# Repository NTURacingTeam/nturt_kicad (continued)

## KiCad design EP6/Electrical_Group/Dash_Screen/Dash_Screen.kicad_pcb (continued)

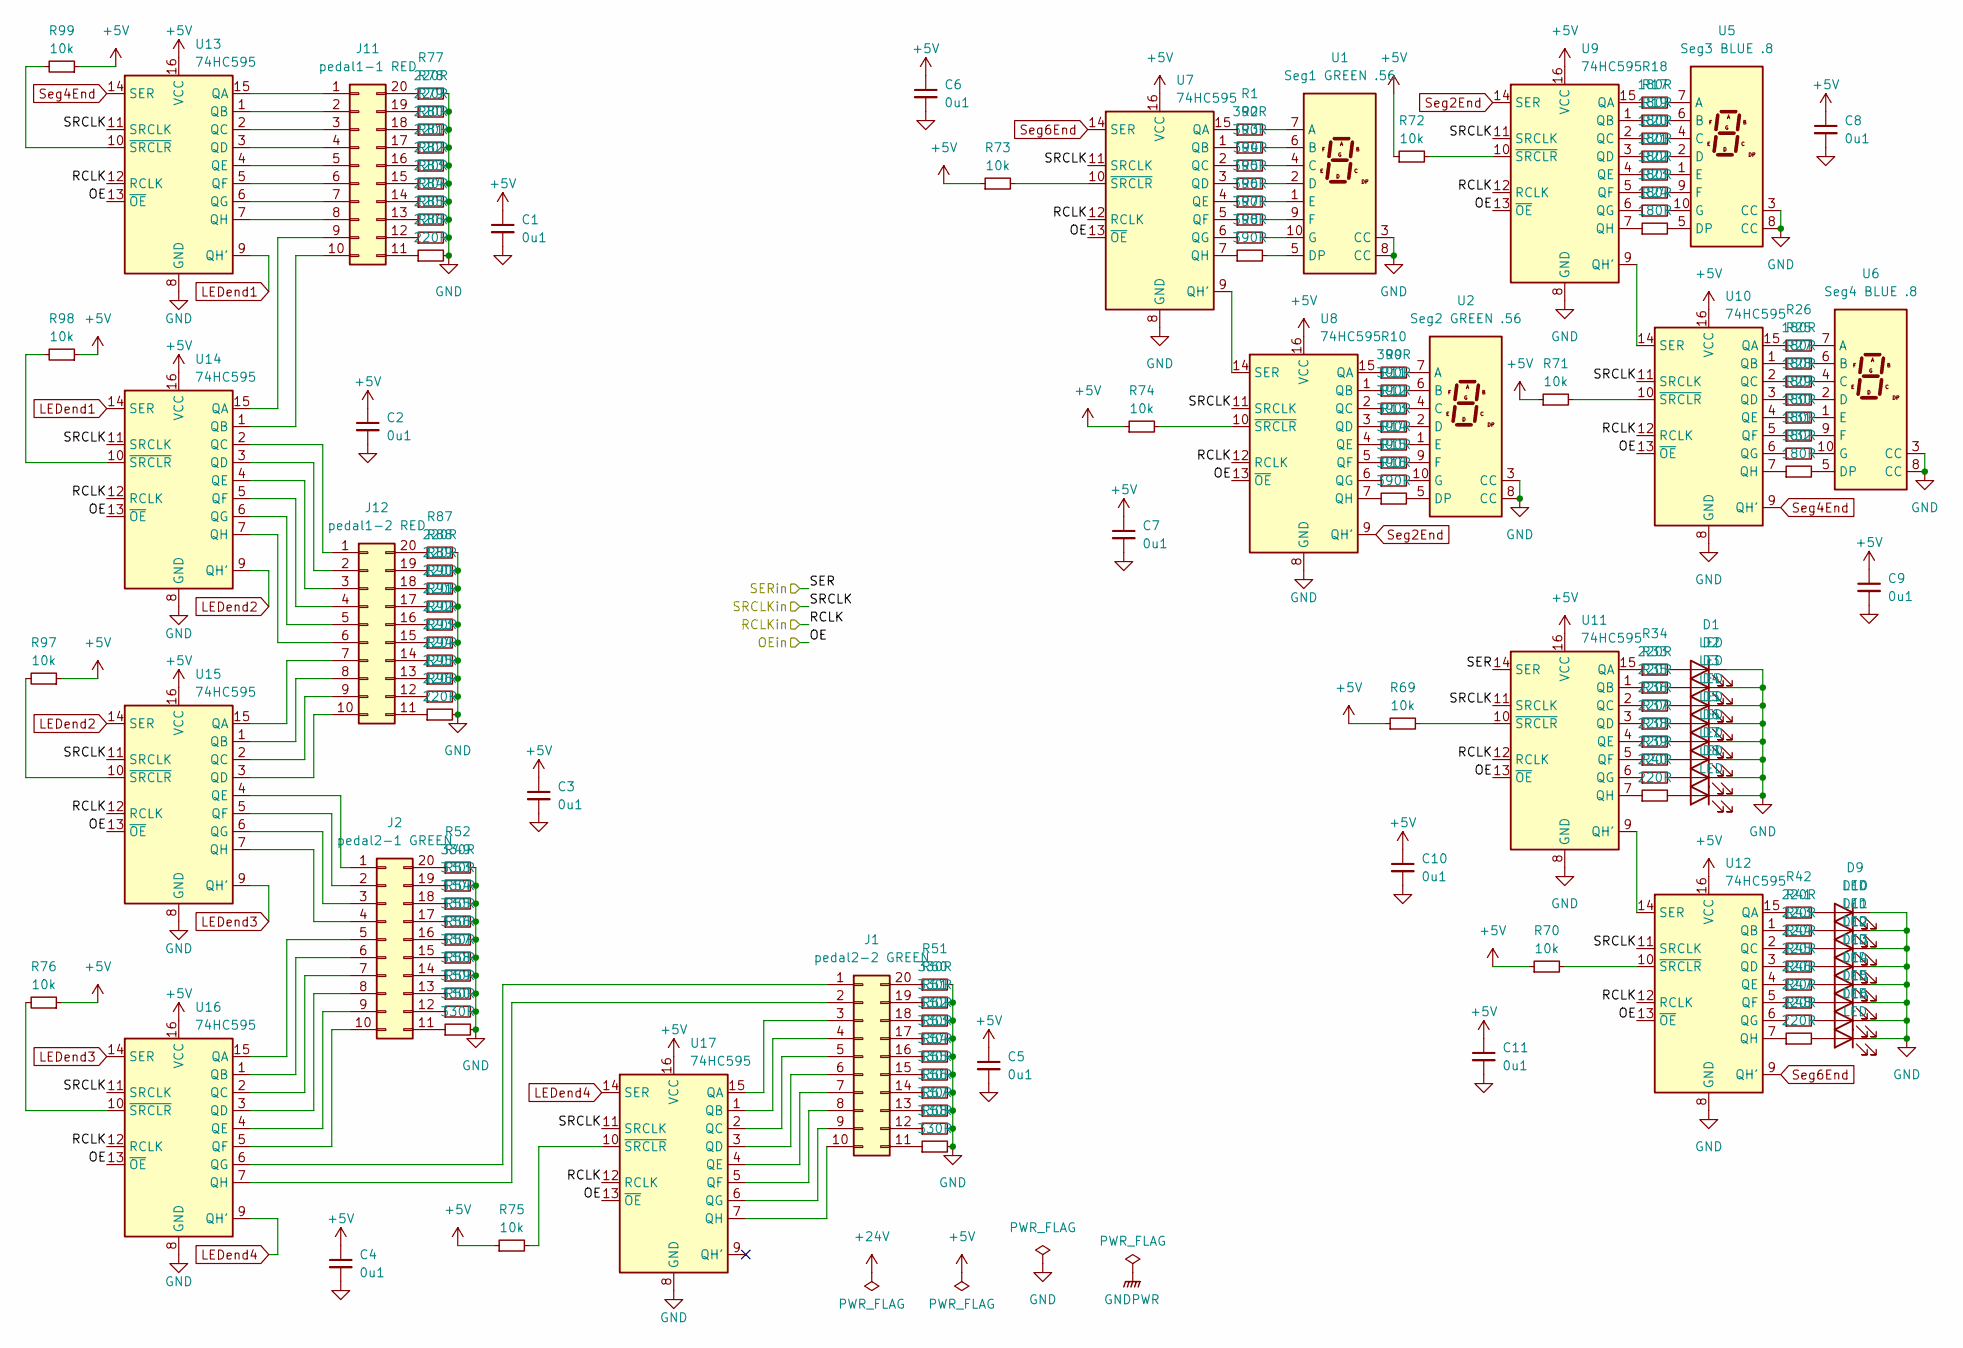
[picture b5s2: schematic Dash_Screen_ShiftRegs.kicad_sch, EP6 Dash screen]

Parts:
C1, C2, C3, C4, C5, C6, C7, C8, C9, C10, C11: 0u1; C_0805_2012Metric
D1, D2, D3, D4, D5, D6, D7, D8, D9, D10, D11, D12, D13, D14, D15, D16: LED; LED_PLCC_2835_Handsoldering
J1: pedal2-2 GREEN; DIP-20_W7.62mm
J2: pedal2-1 GREEN; DIP-20_W7.62mm
J11: pedal1-1 RED; DIP-20_W7.62mm
J12: pedal1-2 RED; DIP-20_W7.62mm
R1, R2, R3, R4, R5, R6, R7, R8, R9, R10, R11, R12, R13, R14, R15, R16: 390R; R_0603_1608Metric_Pad0.98x0.95mm_HandSolder
R17, R18, R19, R20, R21, R22, R23, R24, R25, R26, R27, R28, R29, R30, R31, R32: 180R; R_0603_1608Metric_Pad0.98x0.95mm_HandSolder
R33, R34, R35, R36, R37, R38, R39, R40, R41, R42, R43, R44, R45, R46, R47, R48, R77, R78, R79, R80, R81, R82, R83, R84, R85, R86, R87, R88, R89, R90, R91, R92, R93, R94, R95, R96: 220R; R_0603_1608Metric_Pad0.98x0.95mm_HandSolder
R49, R50, R51, R52, R53, R54, R55, R56, R57, R58, R59, R60, R61, R62, R63, R64, R65, R66, R67, R68: 330R; R_0603_1608Metric_Pad0.98x0.95mm_HandSolder
R69, R70, R71, R72, R73, R74, R75, R76, R97, R98, R99: 10k; R_0603_1608Metric
U1: Seg1 GREEN .56; 7SegmentLED_LTS6760_LTS6780
U2: Seg2 GREEN .56; 7SegmentLED_LTS6760_LTS6780
U5: Seg3 BLUE .8; 7SEGMENT-08inch
U6: Seg4 BLUE .8; 7SEGMENT-08inch
U7, U8, U9, U10, U11, U12, U13, U14, U15, U16, U17: 74HC595; SOIC-16_3.9x9.9mm_P1.27mm

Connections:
+5V: C1.1, C2.1, C3.1, C4.1, C5.1, C6.1, C7.1, C8.1, C9.1, C10.1, C11.1, R69.1, R70.1, R71.1, R72.1, R73.1, R74.1, R75.1, R76.1, R97.1, R98.1, R99.1, U7.16 (VCC), U8.16 (VCC), U9.16 (VCC), U10.16 (VCC), U11.16 (VCC), U12.16 (VCC), U13.16 (VCC), U14.16 (VCC), U15.16 (VCC), U16.16 (VCC), U17.16 (VCC); also elsewhere on the board
/Dash_Screen_ShiftRegs/OE: U7.13 (~OE), U8.13 (~OE), U9.13 (~OE), U10.13 (~OE), U11.13 (~OE), U12.13 (~OE), U13.13 (~OE), U14.13 (~OE), U15.13 (~OE), U16.13 (~OE), U17.13 (~OE); also elsewhere on the board
/Dash_Screen_ShiftRegs/RCLK: U7.12 (RCLK), U8.12 (RCLK), U9.12 (RCLK), U10.12 (RCLK), U11.12 (RCLK), U12.12 (RCLK), U13.12 (RCLK), U14.12 (RCLK), U15.12 (RCLK), U16.12 (RCLK), U17.12 (RCLK); also elsewhere on the board
/Dash_Screen_ShiftRegs/SER: U11.14 (SER); also elsewhere on the board
/Dash_Screen_ShiftRegs/SRCLK: U7.11 (SRCLK), U8.11 (SRCLK), U9.11 (SRCLK), U10.11 (SRCLK), U11.11 (SRCLK), U12.11 (SRCLK), U13.11 (SRCLK), U14.11 (SRCLK), U15.11 (SRCLK), U16.11 (SRCLK), U17.11 (SRCLK); also elsewhere on the board
GND: C1.2, C2.2, C3.2, C4.2, C5.2, C6.2, C7.2, C8.2, C9.2, C10.2, C11.2, D1.1 (K), D2.1 (K), D3.1 (K), D4.1 (K), D5.1 (K), D6.1 (K), D7.1 (K), D8.1 (K), D9.1 (K), D10.1 (K), D11.1 (K), D12.1 (K), D13.1 (K), D14.1 (K), D15.1 (K), D16.1 (K), R49.2, R50.2, R51.2, R52.2, R53.2, R54.2, R55.2, R56.2, R57.2, R58.2, R59.2, R60.2, R61.2, R62.2, R63.2, R64.2, R65.2, R66.2, R67.2, R68.2, R77.2, R78.2, R79.2, R80.2, R81.2, R82.2, R83.2, R84.2, R85.2, R86.2, R87.2, R88.2, R89.2, R90.2, R91.2, R92.2, R93.2, R94.2, R95.2, R96.2, U1.3 (CC), U1.8 (CC), U2.3 (CC), U2.8 (CC), U5.3 (CC), U5.8 (CC), U6.3 (CC), U6.8 (CC), U7.8 (GND), U8.8 (GND), U9.8 (GND), U10.8 (GND), U11.8 (GND), U12.8 (GND), U13.8 (GND), U14.8 (GND), U15.8 (GND), U16.8 (GND), U17.8 (GND); also elsewhere on the board
LEDend1: U13.9 (QH'), U14.14 (SER)
LEDend2: U14.9 (QH'), U15.14 (SER)
LEDend3: U15.9 (QH'), U16.14 (SER)
LEDend4: U16.9 (QH'), U17.14 (SER)
unnamed: D1.2 (A), R34.2
unnamed: D2.2 (A), R33.2
unnamed: D3.2 (A), R35.2
unnamed: D4.2 (A), R36.2
unnamed: D5.2 (A), R37.2
unnamed: D6.2 (A), R38.2
unnamed: D7.2 (A), R39.2
unnamed: D8.2 (A), R40.2
unnamed: D9.2 (A), R42.2
unnamed: D10.2 (A), R41.2
unnamed: D11.2 (A), R43.2
unnamed: D12.2 (A), R44.2
unnamed: D13.2 (A), R45.2
unnamed: D14.2 (A), R46.2
unnamed: D15.2 (A), R47.2
unnamed: D16.2 (A), R48.2
unnamed: J1.1, U16.6 (QG)
unnamed: J1.2, U16.7 (QH)
unnamed: J1.3, U17.15 (QA)
unnamed: J1.4, U17.1 (QB)
unnamed: J1.5, U17.2 (QC)
unnamed: J1.6, U17.3 (QD)
unnamed: J1.7, U17.4 (QE)
unnamed: J1.8, U17.5 (QF)
unnamed: J1.9, U17.6 (QG)
unnamed: J1.10, U17.7 (QH)
unnamed: J1.11, R68.1
unnamed: J1.12, R67.1
unnamed: J1.13, R66.1
unnamed: J1.14, R65.1
unnamed: J1.15, R64.1
unnamed: J1.16, R63.1
unnamed: J1.17, R62.1
unnamed: J1.18, R61.1
unnamed: J1.19, R60.1
unnamed: J1.20, R51.1
unnamed: J2.1, U15.4 (QE)
unnamed: J2.2, U15.5 (QF)
unnamed: J2.3, U15.6 (QG)
unnamed: J2.4, U15.7 (QH)
unnamed: J2.5, U16.15 (QA)
unnamed: J2.6, U16.1 (QB)
unnamed: J2.7, U16.2 (QC)
unnamed: J2.8, U16.3 (QD)
unnamed: J2.9, U16.4 (QE)
unnamed: J2.10, U16.5 (QF)
unnamed: J2.11, R50.1
unnamed: J2.12, R59.1
unnamed: J2.13, R58.1
unnamed: J2.14, R57.1
unnamed: J2.15, R56.1
unnamed: J2.16, R55.1
unnamed: J2.17, R54.1
unnamed: J2.18, R53.1
unnamed: J2.19, R49.1
unnamed: J2.20, R52.1
unnamed: J11.1, U13.15 (QA)
unnamed: J11.2, U13.1 (QB)
unnamed: J11.3, U13.2 (QC)
unnamed: J11.4, U13.3 (QD)
unnamed: J11.5, U13.4 (QE)
unnamed: J11.6, U13.5 (QF)
unnamed: J11.7, U13.6 (QG)
unnamed: J11.8, U13.7 (QH)
unnamed: J11.9, U14.15 (QA)
unnamed: J11.10, U14.1 (QB)
unnamed: J11.11, R86.1
unnamed: J11.12, R85.1
unnamed: J11.13, R84.1
unnamed: J11.14, R83.1
unnamed: J11.15, R82.1
unnamed: J11.16, R81.1
unnamed: J11.17, R80.1
unnamed: J11.18, R79.1
unnamed: J11.19, R78.1
unnamed: J11.20, R77.1
unnamed: J12.1, U14.2 (QC)
unnamed: J12.2, U14.3 (QD)
unnamed: J12.3, U14.4 (QE)
unnamed: J12.4, U14.5 (QF)
unnamed: J12.5, U14.6 (QG)
unnamed: J12.6, U14.7 (QH)
unnamed: J12.7, U15.15 (QA)
unnamed: J12.8, U15.1 (QB)
unnamed: J12.9, U15.2 (QC)
unnamed: J12.10, U15.3 (QD)
unnamed: J12.11, R96.1
unnamed: J12.12, R95.1
unnamed: J12.13, R94.1
unnamed: J12.14, R93.1
unnamed: J12.15, R92.1
unnamed: J12.16, R91.1
unnamed: J12.17, R90.1
unnamed: J12.18, R89.1
unnamed: J12.19, R88.1
unnamed: J12.20, R87.1
unnamed: R1.2, U1.7 (A)
unnamed: R2.2, U1.6 (B)
unnamed: R3.2, U1.4 (C)
unnamed: R4.2, U1.2 (D)
unnamed: R8.2, U1.5 (DP)
unnamed: R5.2, U1.1 (E)
unnamed: R6.2, U1.9 (F)
unnamed: R7.2, U1.10 (G)
unnamed: R10.2, U2.7 (A)
unnamed: R9.2, U2.6 (B)
unnamed: R11.2, U2.4 (C)
unnamed: R12.2, U2.2 (D)
unnamed: R16.2, U2.5 (DP)
unnamed: R13.2, U2.1 (E)
unnamed: R14.2, U2.9 (F)
unnamed: R15.2, U2.10 (G)
unnamed: R18.2, U5.7 (A)
unnamed: R17.2, U5.6 (B)
unnamed: R19.2, U5.4 (C)
unnamed: R20.2, U5.2 (D)
unnamed: R24.2, U5.5 (DP)
unnamed: R21.2, U5.1 (E)
unnamed: R22.2, U5.9 (F)
unnamed: R23.2, U5.10 (G)
unnamed: R26.2, U6.7 (A)
unnamed: R25.2, U6.6 (B)
unnamed: R27.2, U6.4 (C)
unnamed: R28.2, U6.2 (D)
unnamed: R32.2, U6.5 (DP)
unnamed: R29.2, U6.1 (E)
unnamed: R30.2, U6.9 (F)
unnamed: R31.2, U6.10 (G)
unnamed: R1.1, U7.15 (QA)
unnamed: R2.1, U7.1 (QB)
unnamed: R3.1, U7.2 (QC)
unnamed: R4.1, U7.3 (QD)
unnamed: R5.1, U7.4 (QE)
unnamed: R6.1, U7.5 (QF)
unnamed: R7.1, U7.6 (QG)
unnamed: U7.9 (QH'), U8.14 (SER)
unnamed: R8.1, U7.7 (QH)
unnamed: R73.2, U7.10 (~SRCLR)
unnamed: R10.1, U8.15 (QA)
unnamed: R9.1, U8.1 (QB)
unnamed: R11.1, U8.2 (QC)
unnamed: R12.1, U8.3 (QD)
unnamed: R13.1, U8.4 (QE)
unnamed: R14.1, U8.5 (QF)
unnamed: R15.1, U8.6 (QG)
unnamed: R16.1, U8.7 (QH)
unnamed: R74.2, U8.10 (~SRCLR)
unnamed: R18.1, U9.15 (QA)
unnamed: R17.1, U9.1 (QB)
unnamed: R19.1, U9.2 (QC)
unnamed: R20.1, U9.3 (QD)
unnamed: R21.1, U9.4 (QE)
unnamed: R22.1, U9.5 (QF)
unnamed: R23.1, U9.6 (QG)
unnamed: R24.1, U9.7 (QH)
unnamed: R72.2, U9.10 (~SRCLR)
unnamed: R26.1, U10.15 (QA)
unnamed: R25.1, U10.1 (QB)
unnamed: R27.1, U10.2 (QC)
unnamed: R28.1, U10.3 (QD)
unnamed: R29.1, U10.4 (QE)
unnamed: R30.1, U10.5 (QF)
unnamed: R31.1, U10.6 (QG)
unnamed: R32.1, U10.7 (QH)
unnamed: U9.9 (QH'), U10.14 (SER)
unnamed: R71.2, U10.10 (~SRCLR)
unnamed: R34.1, U11.15 (QA)
unnamed: R33.1, U11.1 (QB)
unnamed: R35.1, U11.2 (QC)
unnamed: R36.1, U11.3 (QD)
unnamed: R37.1, U11.4 (QE)
unnamed: R38.1, U11.5 (QF)
unnamed: R39.1, U11.6 (QG)
unnamed: U11.9 (QH'), U12.14 (SER)
unnamed: R40.1, U11.7 (QH)
unnamed: R69.2, U11.10 (~SRCLR)
unnamed: R42.1, U12.15 (QA)
unnamed: R41.1, U12.1 (QB)
unnamed: R43.1, U12.2 (QC)
unnamed: R44.1, U12.3 (QD)
unnamed: R45.1, U12.4 (QE)
unnamed: R46.1, U12.5 (QF)
unnamed: R47.1, U12.6 (QG)
unnamed: R48.1, U12.7 (QH)
unnamed: R70.2, U12.10 (~SRCLR)
unnamed: R99.2, U13.10 (~SRCLR)
unnamed: R98.2, U14.10 (~SRCLR)
unnamed: R97.2, U15.10 (~SRCLR)
unnamed: R76.2, U16.10 (~SRCLR)
unnamed: R75.2, U17.10 (~SRCLR)
Seg2End: U8.9 (QH'), U9.14 (SER)
Seg4End: U10.9 (QH'), U13.14 (SER)
Seg6End: U7.14 (SER), U12.9 (QH')

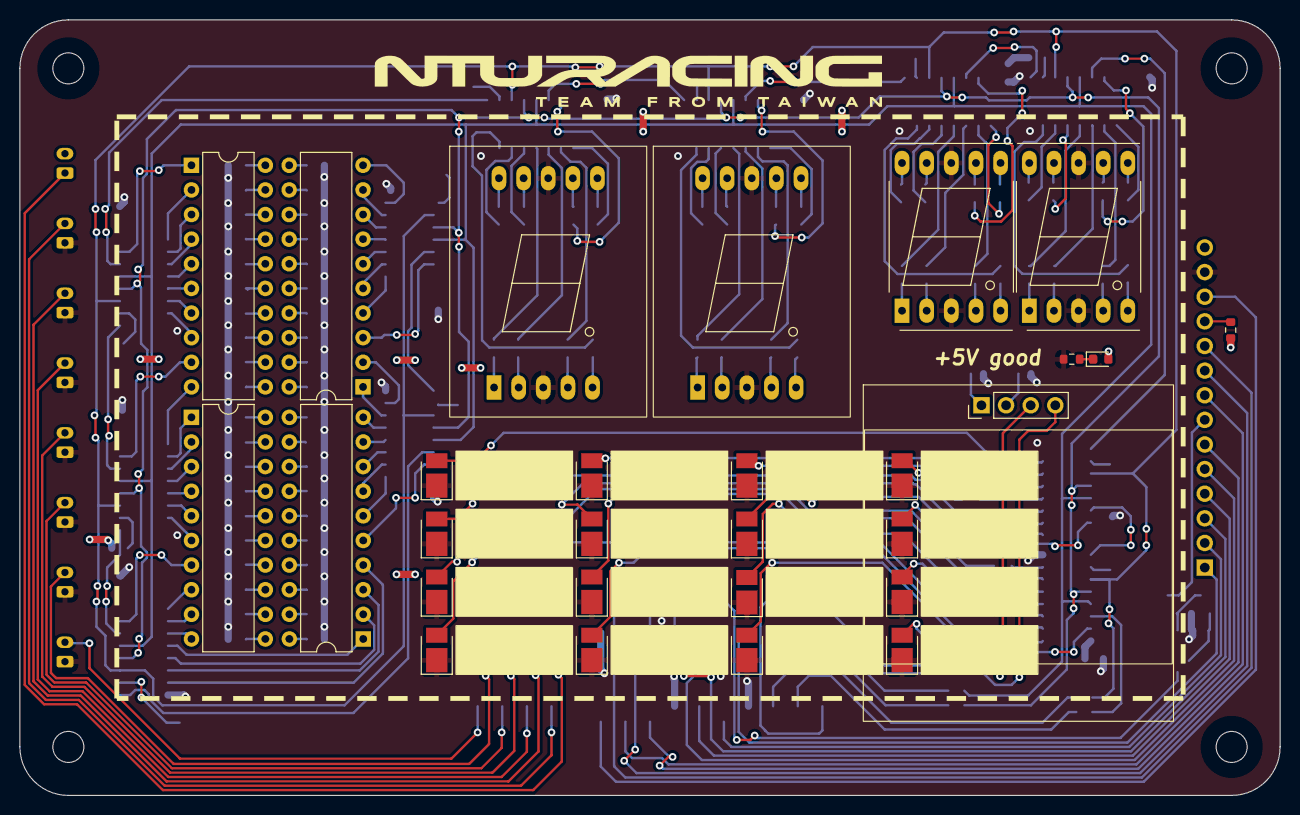
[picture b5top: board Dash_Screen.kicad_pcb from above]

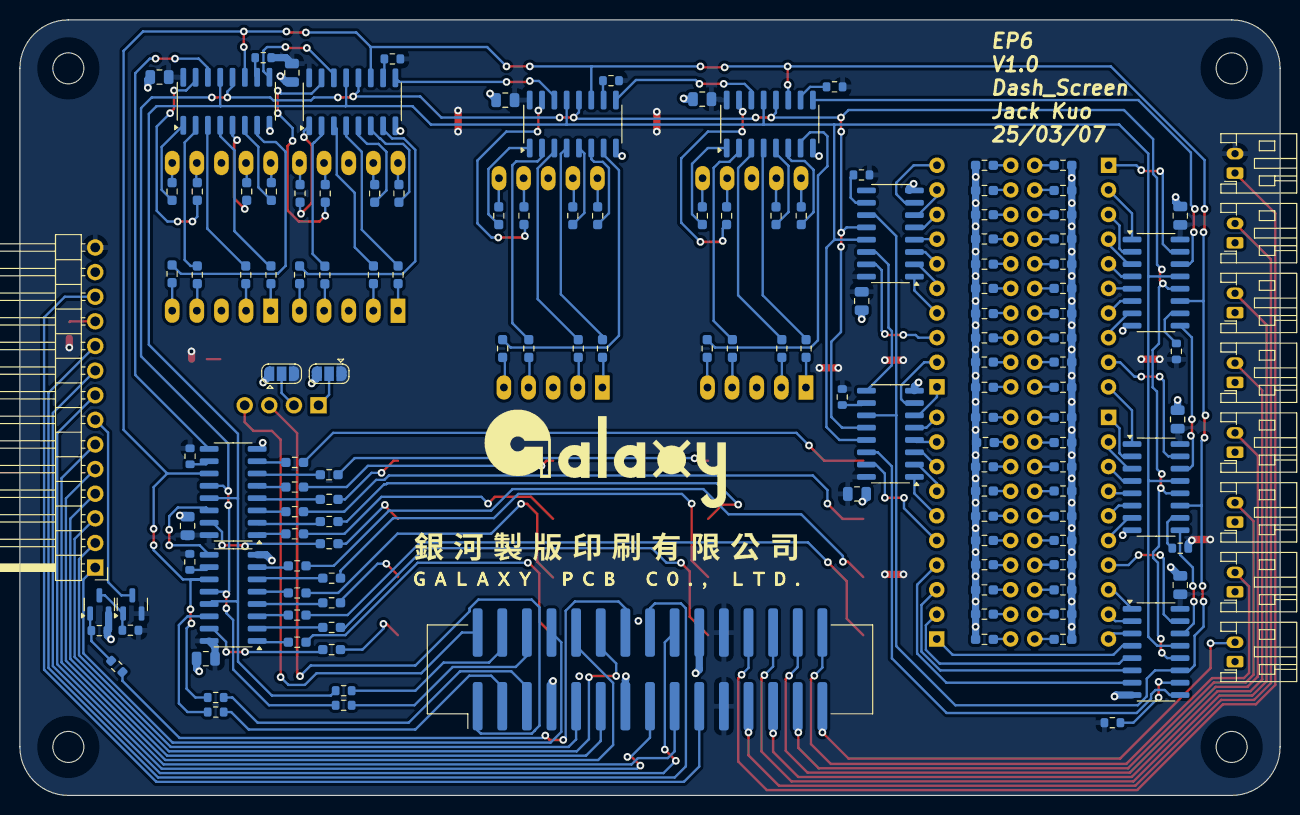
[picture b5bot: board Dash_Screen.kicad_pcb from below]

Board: 2 copper layers, 130.0 x 80.0 mm, 174 parts (142 on the bottom side), 235 nets.

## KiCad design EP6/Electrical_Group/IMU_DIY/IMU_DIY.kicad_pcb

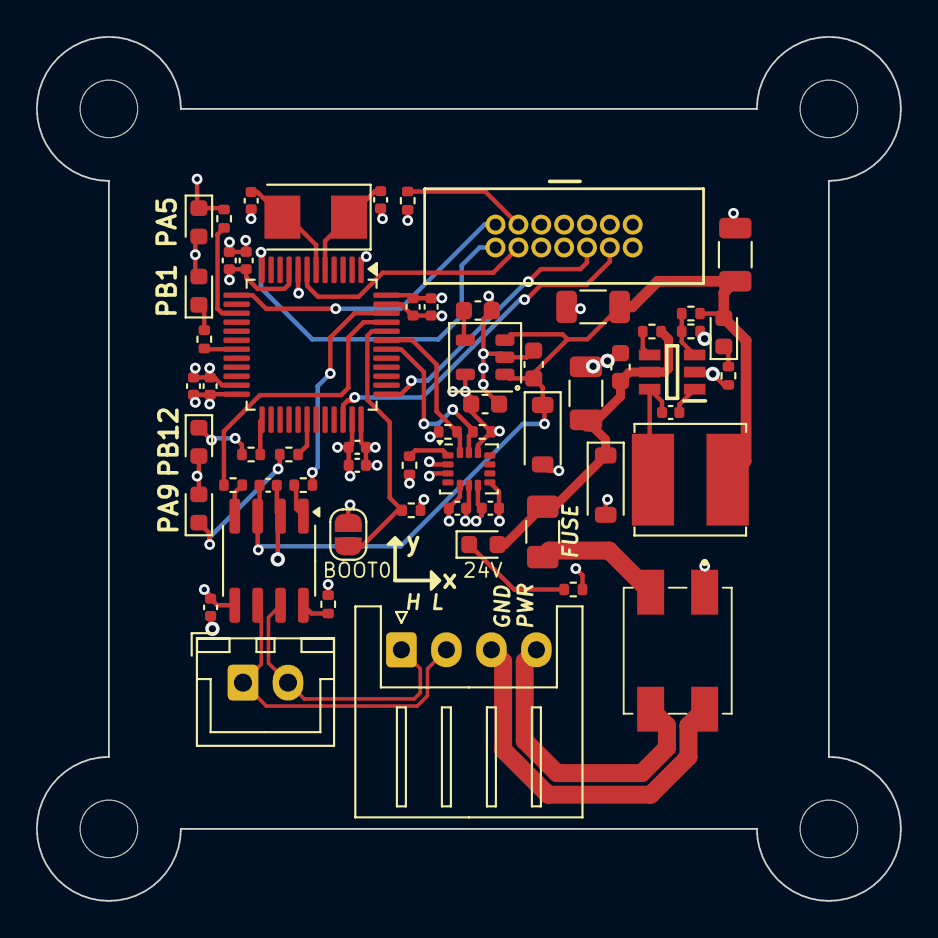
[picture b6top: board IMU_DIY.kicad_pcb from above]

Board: 4 copper layers, 48.0 x 48.0 mm, 64 parts (0 on the bottom side), 41 nets.

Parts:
C1, C2, C3, C4: 10u 6V; C_0402_1005Metric
C5, C6, C7, C8, C11, C65, C66, C89, C90: 0u1; C_0402_1005Metric
C9, C10: 30p; C_0402_1005Metric
C12, C13: 1u; C_0603_1608Metric
C14: 22n; C_0603_1608Metric
C15, C16: 22u 25V; C_1206_3216Metric
C45: 10u 35V; C_1206_3216Metric
C93: 0u1; C_0603_1608Metric
D1: 5.7V MMSZ5233B-7-F; D_SOD-123
D2: RED 24V; LED_0603_1608Metric
D3: RED 5V; LED_0603_1608Metric
D4: WHITE LED; LED_0603_1608Metric
D5: GREEN LED; LED_0603_1608Metric
D6: YELLOW LED; LED_0603_1608Metric
D16: BLUE LED; LED_0603_1608Metric
D32: 27V MMSZ5254B-7-F; D_SOD-123
F1: 0.5A; Fuse_1206_3216Metric
FL1: ACM70V-701-2PL-TL00; ACM70V7012PLTL00
H1, H2, H3, H4: MountingHole; MountingHole_3.2mm_M3
IC1: LMR50410Y3FQDBVRQ1; SOT95P280X145-6N
J2: Conn_01x04; JST_XH_S4B-XH-A_1x04_P2.50mm_Horizontal
J3: STDC14; box_header_14P_pitch127
J4: CAN; JST_XH_B2B-XH-A_1x02_P2.50mm_Vertical
JP3: boot0; SolderJumper-2_P1.3mm_Open_RoundedPad1.0x1.5mm
L5: 47u 1.6A (SRN6045TA-470M); L_Bourns_SRN6045TA
R3, R7, R12, R13: 1k; R_0402_1005Metric
R4, R76, R77: 100R; R_0402_1005Metric
R5, R6, R17, R19, R20, R51: 10k; R_0402_1005Metric
R11: 8k2; R_0402_1005Metric
R18: 2k; R_0402_1005Metric
R72, R74: 3k3; R_0402_1005Metric
U1: STM32F103C8Tx; LQFP-48_7x7mm_P0.5mm
U3: RT9193; SOT-23-5
U4: LSM6DSO32; LGA-14_3x2.5mm_P0.5mm_LayoutBorder3x4y
U11: TCAN1042VDRQ1; SOIC-8_3.9x4.9mm_P1.27mm
Y1: 8MHz X49SM8MSD2SC; Crystal_SMD_5032-2Pin_5.0x3.2mm

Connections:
+3V3: C1.1, C2.1, C3.1, C4.1, C5.1, C6.1, C7.1, C8.1, C13.1, C66.1, C89.2, C90.2, D4.2 (A), D5.2 (A), D6.2 (A), D16.2 (A), J3.3, JP3.2 (B), R72.1, R74.1, U1.1 (VBAT), U1.9 (VDDA), U1.24 (VDD), U1.36 (VDD), U1.48 (VDD), U3.5 (OUT), U4.5 (VDDIO), U4.8 (VDD), U4.12 (CS), U11.5 (VIO)
+5V: C12.1, C15.1, C16.1, C65.1, D1.1 (K), D3.2 (A), L5.2, R11.1, U3.1 (IN), U3.3 (EN), U11.3 (VCC)
+24V: C45.1, C93.2, D2.2 (A), D32.1 (K), F1.2, IC1.5 (VIN), R20.1
+24V_preCMfilter: FL1.3, J2.4
/5V_3V3/5V_buck_FB: IC1.3 (FB), R11.2, R18.1
/5V_3V3/5V_buck_sw: C11.1, IC1.6 (SW), L5.1
/BOOT0: JP3.1 (A), R5.2, U1.44 (BOOT0)
/CAN_RX: R77.1, U1.45 (PB8)
/CAN_TX: R76.1, U1.46 (PB9)
/I2C1_SCL: R72.2, U1.42 (PB6), U4.13 (SCL)
/I2C1_SDA: R74.2, U1.43 (PB7), U4.14 (SDA)
/NRST: J3.12, U1.7 (NRST)
/OSC_IN: C9.1, U1.5 (PD0), Y1.1
/OSC_OUT: C10.1, U1.6 (PD1), Y1.2
/SWCLK: J3.6, U1.37 (PA14)
/SWDIO: J3.4, U1.34 (PA13)
/USART2_RX: J3.13, U1.13 (PA3)
/USART2_TX: J3.14, U1.12 (PA2)
/electrical1/CANH: J2.1, J4.2, U11.7 (CANH)
/electrical1/CANL: J2.2, J4.1, U11.6 (CANL)
/power/+24V_prefuse: F1.1, FL1.2
GND: C1.2, C2.2, C3.2, C4.2, C5.2, C6.2, C7.2, C8.2, C9.2, C10.2, C12.2, C13.2, C14.2, C15.2, C16.2, C45.2, C65.2, C66.2, C89.1, C90.1, C93.1, D1.2 (A), D32.2 (A), FL1.1, IC1.2 (GND), J3.5, J3.7, R4.1, R5.1, R6.1, R17.2, R18.2, R19.2, R51.2, U1.8 (VSSA), U1.23 (VSS), U1.35 (VSS), U1.47 (VSS), U3.2, U4.2 (SDX), U4.3 (SCX), U4.6 (GND), U4.7 (GND), U11.2 (GND)
GNDPWR: FL1.4, J2.3
unnamed: D2.1 (K), R17.1
unnamed: D3.1 (K), R19.1
unnamed: D4.1 (K), R3.1
unnamed: D5.1 (K), R12.1
unnamed: D6.1 (K), R13.1
unnamed: D16.1 (K), R7.1
unnamed: C11.2, IC1.1 (CB)
unnamed: IC1.4 (EN), R20.2
unnamed: J3.11, R4.2
unnamed: R7.2, U1.15 (PA5)
unnamed: R13.2, U1.30 (PA9)
unnamed: R12.2, U1.19 (PB1)
unnamed: R3.2, U1.25 (PB12)
unnamed: C14.1, U3.4 (BYP)
unnamed: R6.2, U4.1 (SDO/SA0)
unnamed: R77.2, U11.4 (RXD)
unnamed: R51.1, U11.8 (STB)
unnamed: R76.2, U11.1 (TXD)
